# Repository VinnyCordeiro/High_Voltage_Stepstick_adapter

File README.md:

# High Voltage Stepstick adapter

## DANGER! THIS ADAPTER, AS OF AUGUST 24TH, 2021, IS UNTESTED AND CAN DAMAGE YOUR 3D PRINTER BOARD IF YOU DO NOT FOLLOW THE INSTRUCTIONS TO THE LETTER. I AM NOT RESPONSIBLE FOR WHATEVER YOU DO ON YOUR HARDWARE, YOU HAVE BEEN WARNED.

This board is a simple adapter for usage of high voltage ( > 24V ) on 3D printer boards. TMC5160 stepstick drivers are becoming more popular because they have a high voltage version that can handle up to 50V, made by Watterott. Using higher voltages, the driver can overcome more stepper motor backvoltage that are induced by high speeds, meaning you can go even faster.

This adapter can be used only on boards where the stepsticks are place on "portrait" mode, like Bigtreetech Octopus and Fysetc Spider. Stepsticks on "landscape" mode, like the ones on SKR 2.0, are not supported.

DISCLAIMER: I do not claim being the author of the original idea; that goes to Maze, on the [Mercury One project Discord server](https://discord.gg/t4pf7vYe). I took his idea and made my own spin: the only thing I ever saw from his board was a render showing the components' placement.

### Instructions:

When soldering the socket headers, remove the one that is indicated on the PCB's silkscreen. FAILING TO DO THAT WILL DESTROY YOUR BOARD, YOU HAVE BEEN WARNED.

### Updates

December 09, 2021: added Gerber files, added a Schottky diode between VDD and VMOT lines for safety.

### To-Do:

* Add BOM

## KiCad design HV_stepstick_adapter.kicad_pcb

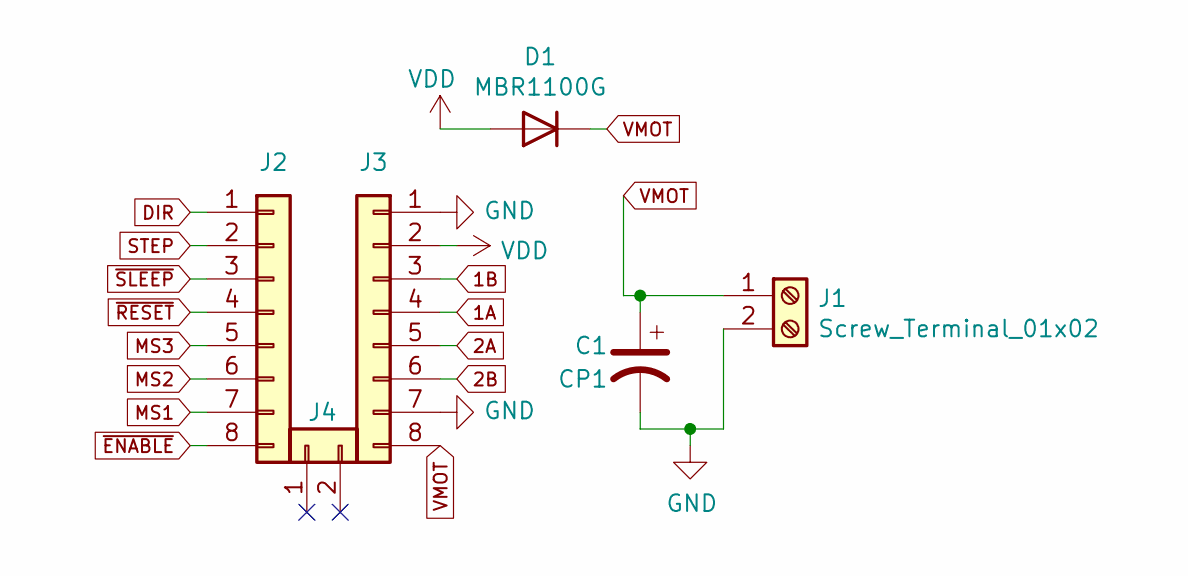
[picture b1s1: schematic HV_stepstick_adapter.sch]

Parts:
C1: CP1; CP_Radial_D12.5mm_P5.00mm
D1: MBR1100G; D_DO-41_SOD81_P10.16mm_Horizontal
J1: Screw_Terminal_01x02; TerminalBlock_Phoenix_MKDS-1,5-2-5.08_1x02_P5.08mm_Horizont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
J2, J3: Conn_01x08; PinSocket_1x08_P2.54mm_Vertical
J4: Conn_01x02; PinSocket_1x02_P2.54mm_Vertical

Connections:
1A: J3.4
1B: J3.3
2A: J3.5
2B: J3.6
DIR: J2.1
GND: C1.2, J1.2, J3.1, J3.7
MS1: J2.7
MS2: J2.6
MS3: J2.5
STEP: J2.2
VDD: D1.2 (A), J3.2
VMOT: C1.1, D1.1 (K), J1.1, J3.8
~ENABLE: J2.8
~RESET: J2.4
~SLEEP: J2.3

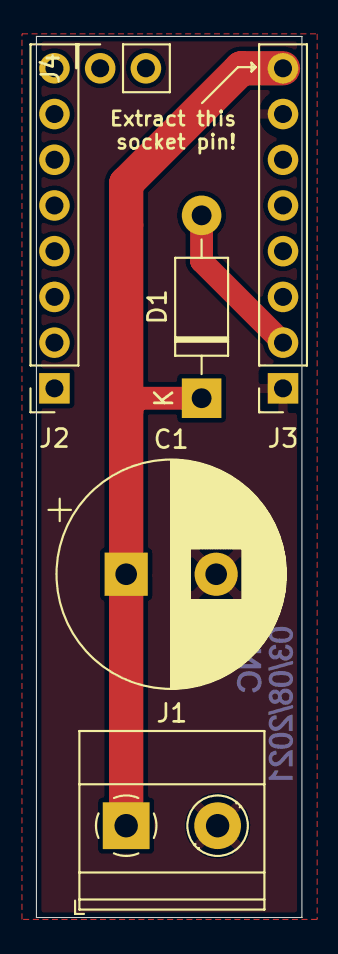
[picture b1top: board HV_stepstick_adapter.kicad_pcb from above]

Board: 2 copper layers, 14.7 x 48.9 mm, 6 parts (0 on the bottom side), 3 nets.

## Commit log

2021-08-24 Update README.md
    Initial commit.
2021-08-24 Add files via upload
    Initial commit
2021-11-11 Update README.md
    Added a disclaimer about PCB idea origin
2021-12-09 Added diode for safety
    Added a Schottky diode between VDD and VMOT lines for safety; also slightly reduced PCB width, to improve the fit on boards; and now Gerber files are available.
